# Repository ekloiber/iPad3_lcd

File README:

Originally:

Schematics of an interface board for connecting an iPad retina display (LP097QX1-SPA1) to a DisplayPort source.

Revised:

PCB for connecting an iPad 3 LCD screen to displayport and using an inexpensive capacitive touch screen digitizer as a USB multi-touch device.

Goals:
- Inexpensive (~$100)
- Accessible for modification
- Open source
- Simple construction 
  - PCB through OSH Park
  - Case through laser-cut acrylic
  - Parts throuh suppliers like AliExpress, Mouser

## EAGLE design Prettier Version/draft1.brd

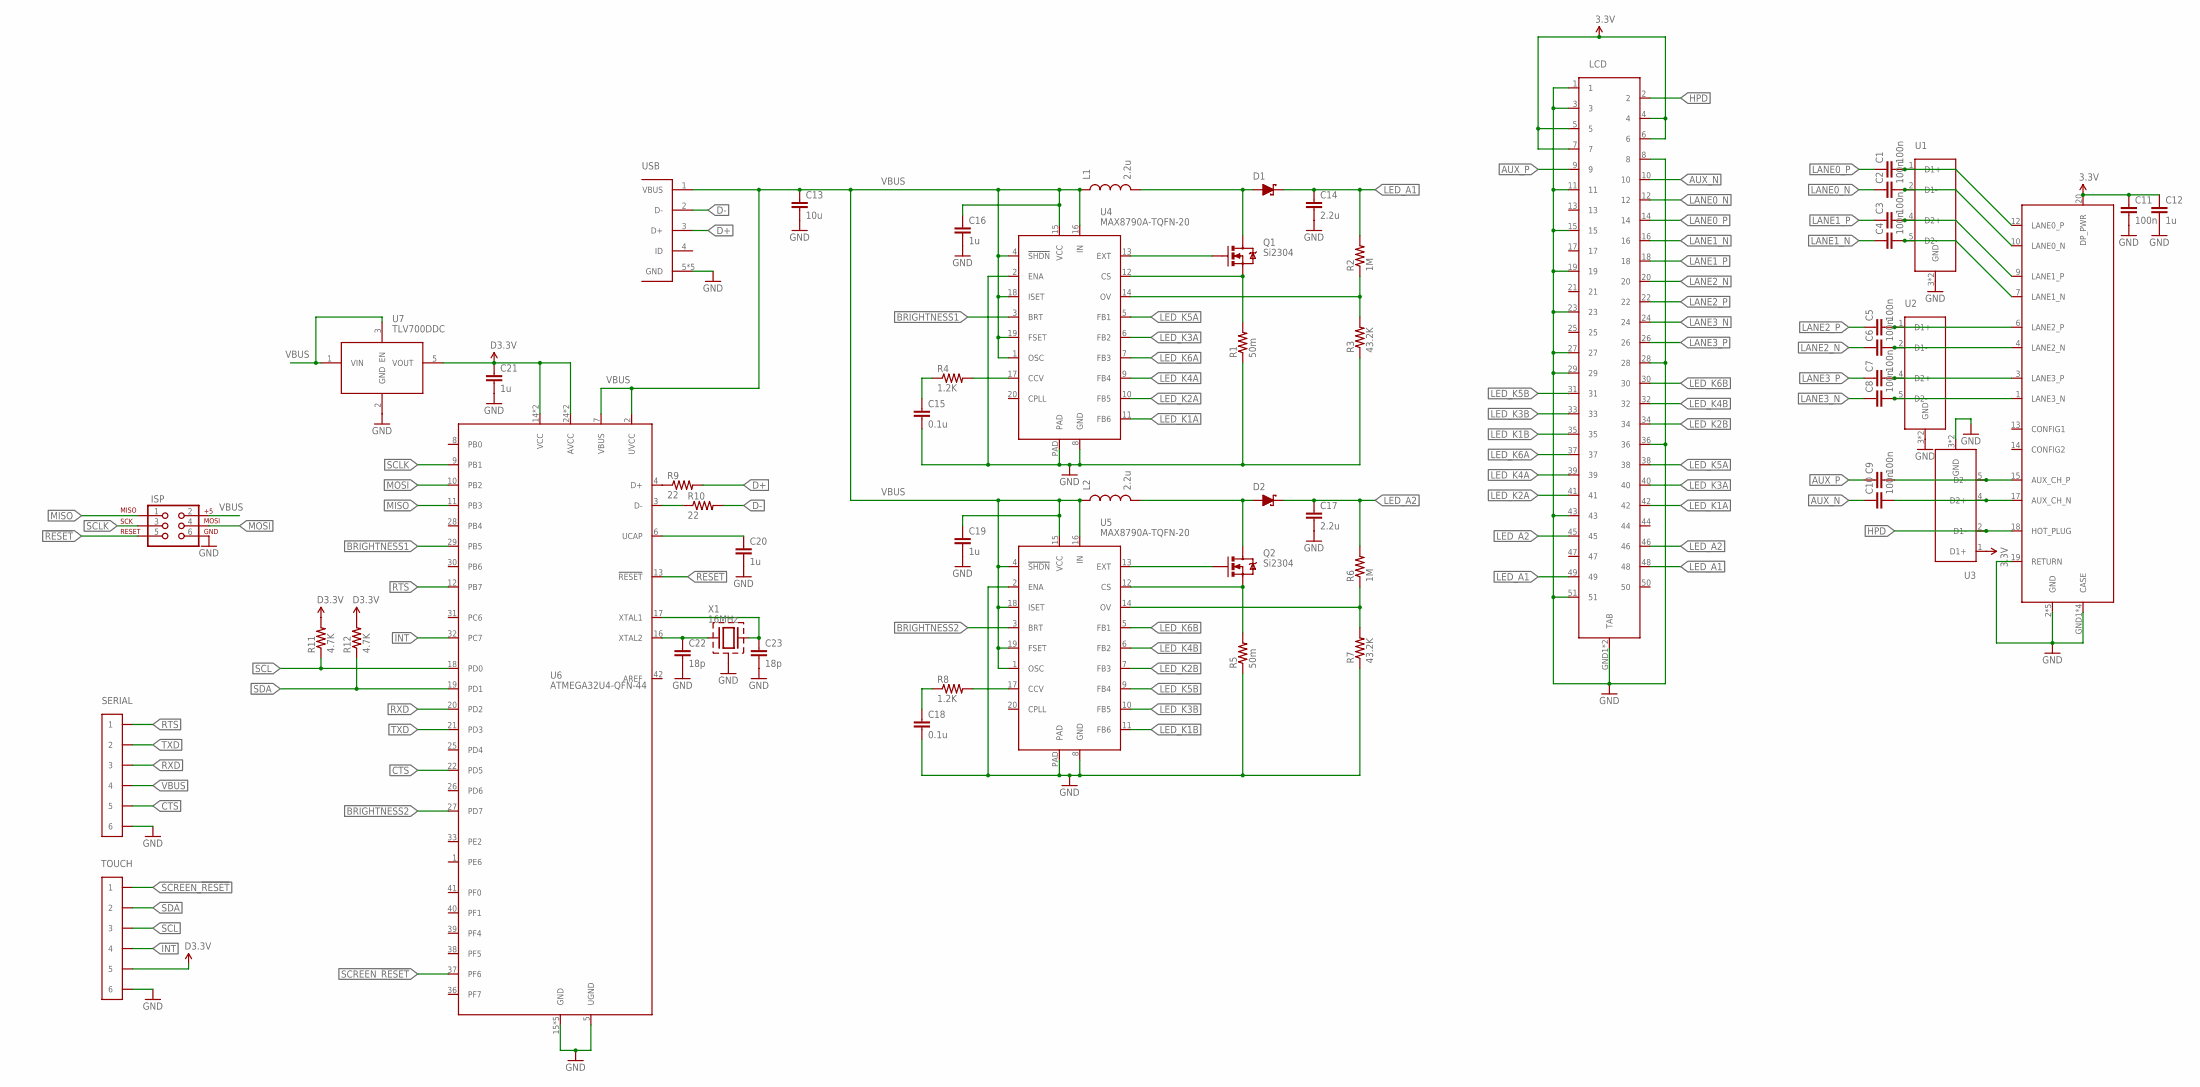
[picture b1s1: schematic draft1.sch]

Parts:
C1, C2, C3, C4, C5, C6, C7, C8, C9, C10: 100n; C0402
C11: 100n; C0805
C12: 1u; C0805
C13: 10u; C1206
C14, C17: 2.2u; C1206
C15, C18: 0.1u; C0603
C16, C19, C20, C21: 1u; C0603
C22, C23: 18p; C0603
D1, D2: DB2W40300L; MINI2-F3-B
DP: DISPLAYPORT-SINK-MOLEX; MOLEX-47272-0028
ISP: AVR_SPI_PRG_6PTH; 2X3
L1, L2: 2.2u; 1210
LCD: CONN-51P-FPC-MOLEX; MOLEX-502250-5191
Q1, Q2: Si2304; SOT23-3
R1, R5: 50m; MCS1632
R2, R6: 1M; R0603
R3, R7: 43.2K; R0603
R4, R8: 1.2K; R0603
R9, R10: 22; R0603
R11, R12: 4.7K; R0603
SERIAL: HEADER-6X1-961106-5500; HEADER-3M-961-6P-2.54MM
TOUCH: HEADER-6X1-FPC-DUAL_CONTACT; MOLEX-503480-0600
U1, U2, U3: ESD-SUPPRESSOR-4-TPD4S010-DQA; SON-10
U4, U5: MAX8790A-TQFN-20; TQFN-20
U6: ATMEGA32U4-QFN-44; QFN-44
U7: TLV700DDC; SOT-23-5
USB: USB_MICRO_AB
X1: 16MHz; ABM3C

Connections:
3.3V: C11.1, C12.1, DP.20 (DP_PWR), LCD.4, LCD.5, LCD.6, LCD.7, U3.1 (D1+)
!RESET: ISP.5, U6.13 (!RESET)
AUX_N: C10.1, LCD.10
AUX_P: C9.1, LCD.9
BRIGHTNESS1: U4.3 (BRT), U6.29 (PB5)
BRIGHTNESS2: U5.3 (BRT), U6.27 (PD7)
CTS: SERIAL.5, U6.22 (PD5)
D3.3V: C21.1, R11.2, R12.2, TOUCH.5, U6.14 (VCC), U6.24 (AVCC), U6.34 (VCC), U6.44 (AVCC), U7.5 (VOUT)
D+: R9.2, USB.3 (D+)
D-: R10.2, USB.2 (D-)
GND: C11.2, C12.2, C13.2, C14.2, C15.2, C16.2, C17.2, C18.2, C19.2, C20.2, C21.2, C22.2, C23.2, DP.2 (GND), DP.5 (GND), DP.8 (GND), DP.11 (GND), DP.16 (GND), DP.19 (RETURN), DP.GND1 (CASE), DP.GND2 (CASE), DP.GND3 (CASE), DP.GND4 (CASE), ISP.6, LCD.1, LCD.3, LCD.8, LCD.11, LCD.15, LCD.19, LCD.23, LCD.27, LCD.28, LCD.29, LCD.36, LCD.43, LCD.51, LCD.GND1 (TAB), LCD.GND2 (TAB), R1.1, R3.1, R5.1, R7.1, SERIAL.6, TOUCH.6, U1.3 (GND), U1.8 (GND), U2.3 (GND), U2.8 (GND), U3.3 (GND), U3.8 (GND), U4.2 (ENA), U4.8 (GND), U4.PAD, U5.2 (ENA), U5.8 (GND), U5.PAD, U6.5 (UGND), U6.15 (GND), U6.23 (GND), U6.35 (GND), U6.43 (GND), U6.PAD (GND), U7.2 (GND), USB.5 (GND), USB.GND1 (GND), USB.GND2 (GND), USB.GND3 (GND), USB.GND4 (GND), X1.2 (CASE), X1.4 (CASE)
HPD: DP.18 (HOT_PLUG), LCD.2, U3.2 (D1-)
INT: TOUCH.4, U6.32 (PC7)
LANE0_N: C2.1, LCD.12
LANE0_P: C1.1, LCD.14
LANE1_N: C4.1, LCD.16
LANE1_P: C3.1, LCD.18
LANE2_N: C6.1, LCD.20
LANE2_P: C5.1, LCD.22
LANE3_N: C8.1, LCD.24
LANE3_P: C7.1, LCD.26
LED_A1: C14.1, D1.1 (K), LCD.48, LCD.49, R2.2
LED_A2: C17.1, D2.1 (K), LCD.45, LCD.46, R6.2
LED_K1A: LCD.42, U4.11 (FB6)
LED_K1B: LCD.35, U5.11 (FB6)
LED_K2A: LCD.41, U4.10 (FB5)
LED_K2B: LCD.34, U5.7 (FB3)
LED_K3A: LCD.40, U4.6 (FB2)
LED_K3B: LCD.33, U5.10 (FB5)
LED_K4A: LCD.39, U4.9 (FB4)
LED_K4B: LCD.32, U5.6 (FB2)
LED_K5A: LCD.38, U4.5 (FB1)
LED_K5B: LCD.31, U5.9 (FB4)
LED_K6A: LCD.37, U4.7 (FB3)
LED_K6B: LCD.30, U5.5 (FB1)
MISO: ISP.1, U6.11 (PB3)
MOSI: ISP.4, U6.10 (PB2)
unnamed: C4.2, DP.7 (LANE1_N), U1.5 (D2-)
unnamed: C3.2, DP.9 (LANE1_P), U1.4 (D2+)
unnamed: C2.2, DP.10 (LANE0_N), U1.2 (D1-)
unnamed: C1.2, DP.12 (LANE0_P), U1.1 (D1+)
unnamed: C5.2, DP.6 (LANE2_P), U2.1 (D1+)
unnamed: C6.2, DP.4 (LANE2_N), U2.2 (D1-)
unnamed: C7.2, DP.3 (LANE3_P), U2.4 (D2+)
unnamed: C8.2, DP.1 (LANE3_N), U2.5 (D2-)
unnamed: C9.2, DP.15 (AUX_CH_P), U3.5 (D2-)
unnamed: C10.2, DP.17 (AUX_CH_N), U3.4 (D2+)
unnamed: Q1.2 (S), R1.2, U4.12 (CS)
unnamed: Q2.1 (G), U5.13 (EXT)
unnamed: Q1.1 (G), U4.13 (EXT)
unnamed: D1.2 (A), L1.2, Q1.3 (D)
unnamed: R2.1, R3.2, U4.14 (OV)
unnamed: R4.2, U4.17 (CCV)
unnamed: C15.1, R4.1
unnamed: D2.2 (A), L2.2, Q2.3 (D)
unnamed: Q2.2 (S), R5.2, U5.12 (CS)
unnamed: R6.1, R7.2, U5.14 (OV)
unnamed: R8.2, U5.17 (CCV)
unnamed: C18.1, R8.1
unnamed: R9.1, U6.4 (D+)
unnamed: R10.1, U6.3 (D-)
unnamed: C20.1, U6.6 (UCAP)
unnamed: C22.1, U6.16 (XTAL2), X1.1
unnamed: C23.1, U6.17 (XTAL1), X1.3 (2)
RTS: SERIAL.1, U6.12 (PB7)
RXD: SERIAL.3, U6.20 (PD2)
SCL: R11.1, TOUCH.3, U6.18 (PD0)
SCLK: ISP.3, U6.9 (PB1)
SCREEN_!RESET: TOUCH.1, U6.37 (PF6)
SDA: R12.1, TOUCH.2, U6.19 (PD1)
TXD: SERIAL.2, U6.21 (PD3)
VBUS: C13.1, C16.1, C19.1, ISP.2, L1.1, L2.1, SERIAL.4, U4.1 (OSC), U4.4 (!SHDN), U4.15 (VCC), U4.16 (IN), U4.18 (ISET), U4.19 (FSET), U5.1 (OSC), U5.4 (!SHDN), U5.15 (VCC), U5.16 (IN), U5.18 (ISET), U5.19 (FSET), U6.2 (UVCC), U6.7 (VBUS), U7.1 (VIN), U7.3 (EN), USB.1 (VBUS)

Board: 4 copper layers, 55 parts (0 on the bottom side), 72 nets, no tracks yet.

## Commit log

2013-04-30 Schematic work
    Added LED control
2013-05-06 Prelim. PCB layout
2013-05-16 Misc updates
2013-05-16 Deleted PCB layout
    Pending physical measurements

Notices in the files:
parts and their libraries:
SparkFun-DiscreteSemi: Licensing: CC v3.0 Share-Alike You are welcome to use this library for commercial purposes.
